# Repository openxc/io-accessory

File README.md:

OpenXC Dock
===========

This repository is a part of the [OpenXC][] project.

This repository contains the documentation and open source design files for an
example OpenXC accessory that provides a generic I/O interface to add sensors
and actuators to a vehicle. The design was originally released by Ford.

This design has yet to be actually prototyped, so YMMV.

## License

Copyright (c) 2014 Ford Motor Company

The electrical and mechanical designs in this repository are available under the
[Creative Commons Attribution 4.0
International](http://creativecommons.org/licenses/by/4.0/deed.en_US) license.

[OpenXC]: http://openxcplatform.com

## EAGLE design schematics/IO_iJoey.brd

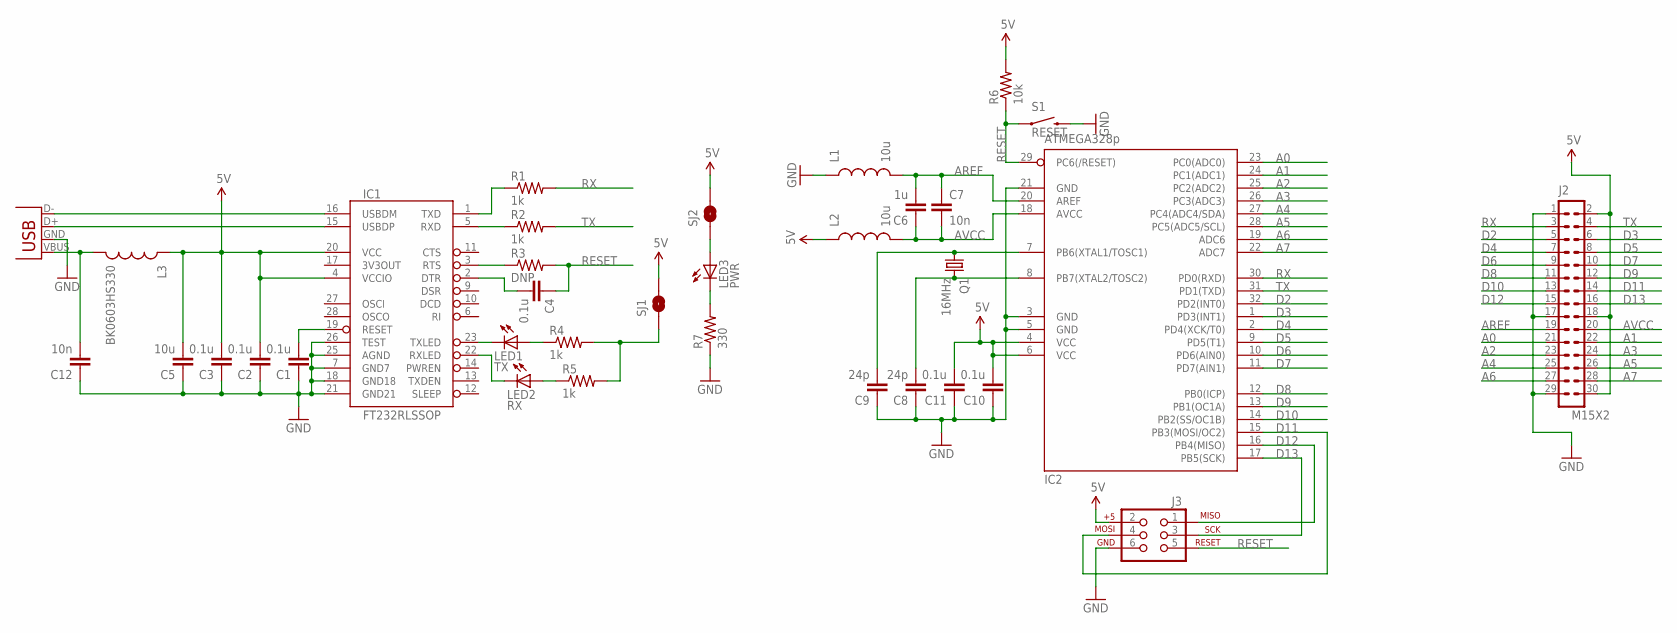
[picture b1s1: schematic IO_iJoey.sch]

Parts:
C1, C2, C3, C4, C10, C11: 0.1u; 0603-CAP
C5: 10u; 0805
C6: 1u; 0603-CAP
C7, C12: 10n; 0603-CAP
C8, C9: 24p; 0603-CAP
IC1: FT232RLSSOP; SSOP28DB
IC2: ATMEGA328p; TQFP32-08
J1: USB-A-H
J2: M15X2; 2X15
J3: AVR_SPI_PRG_6PTH; 2X3
L1, L2: 10u; 0603
L3: BK0603HS330; 0603
LED1: TX; LED-0603
LED2: RX; LED-0603
LED3: PWR; LED-0603
Q1: 16MHz; HC49_GP
R1, R2, R4, R5: 1k; 0603-RES
R3: DNP; 0603-RES
R6: 10k; 0603-RES
R7: 330; 0603-RES
S1: RESET; TACTILE-SWITCH-1101NE
SJ1, SJ2: SOLDERJUMPERNC; SJ_2S

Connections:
5V: C2.2, C3.2, C5.2, C10.2, C11.2, IC1.4 (VCCIO), IC1.20 (VCC), IC2.4 (VCC), IC2.6 (VCC), J2.2, J2.18, J2.30, J3.2, L2.1, L3.1, R6.2, SJ1.2, SJ2.2
A0: IC2.23 (PC0(ADC0)), J2.21
A1: IC2.24 (PC1(ADC1)), J2.22
A2: IC2.25 (PC2(ADC2)), J2.23
A3: IC2.26 (PC3(ADC3)), J2.24
A4: IC2.27 (PC4(ADC4/SDA)), J2.25
A5: IC2.28 (PC5(ADC5/SCL)), J2.26
A6: IC2.19 (ADC6), J2.27
A7: IC2.22 (ADC7), J2.28
AREF: C6.2, C7.1, IC2.20 (AREF), J2.19, L1.2
AVCC: C6.1, C7.2, IC2.18 (AVCC), J2.20, L2.2
D2: IC2.32 (PD2(INT0)), J2.5
D3: IC2.1 (PD3(INT1)), J2.6
D4: IC2.2 (PD4(XCK/T0)), J2.7
D5: IC2.9 (PD5(T1)), J2.8
D6: IC2.10 (PD6(AIN0)), J2.9
D7: IC2.11 (PD7(AIN1)), J2.10
D8: IC2.12 (PB0(ICP)), J2.11
D9: IC2.13 (PB1(OC1A)), J2.12
D10: IC2.14 (PB2(SS/OC1B)), J2.13
D11: IC2.15 (PB3(MOSI/OC2)), J2.14, J3.4
D12: IC2.16 (PB4(MISO)), J2.15, J3.1
D13: IC2.17 (PB5(SCK)), J2.16, J3.3
GND: C1.1, C2.1, C3.1, C5.1, C8.1, C9.1, C10.1, C11.1, C12.1, IC1.7 (GND7), IC1.18 (GND18), IC1.21 (GND21), IC1.25 (AGND), IC1.26 (TEST), IC2.3 (GND), IC2.5 (GND), IC2.21 (GND), J1.GND (VBUS), J2.1, J2.17, J2.29, J3.6, L1.1, R7.1, S1.P$2 (2)
unnamed: IC1.15 (USBDP), J1.D+ (D-)
unnamed: IC1.16 (USBDM), J1.D- (D+)
unnamed: C4.2, IC1.2 (DTR)
unnamed: C1.2, IC1.19 (RESET)
unnamed: C12.2, J1.VBUS (GND), L3.2
unnamed: IC1.3 (RTS), R3.1
unnamed: IC1.5 (RXD), R2.1
unnamed: IC1.1 (TXD), R1.1
unnamed: LED3.C, R7.2
unnamed: IC1.23 (TXLED), LED1.C
unnamed: IC1.22 (RXLED), LED2.C
unnamed: LED2.A, R5.1
unnamed: LED1.A, R4.1
unnamed: R4.2, R5.2, SJ1.1
unnamed: LED3.A, SJ2.1
unnamed: C9.2, IC2.7 (PB6(XTAL1/TOSC1)), Q1.1
unnamed: C8.2, IC2.8 (PB7(XTAL2/TOSC2)), Q1.2
RESET: C4.1, IC2.29 (PC6(/RESET)), J3.5, R3.2, R6.1, S1.P$1 (1)
RX: IC2.30 (PD0(RXD)), J2.3, R1.2
TX: IC2.31 (PD1(TXD)), J2.4, R2.2

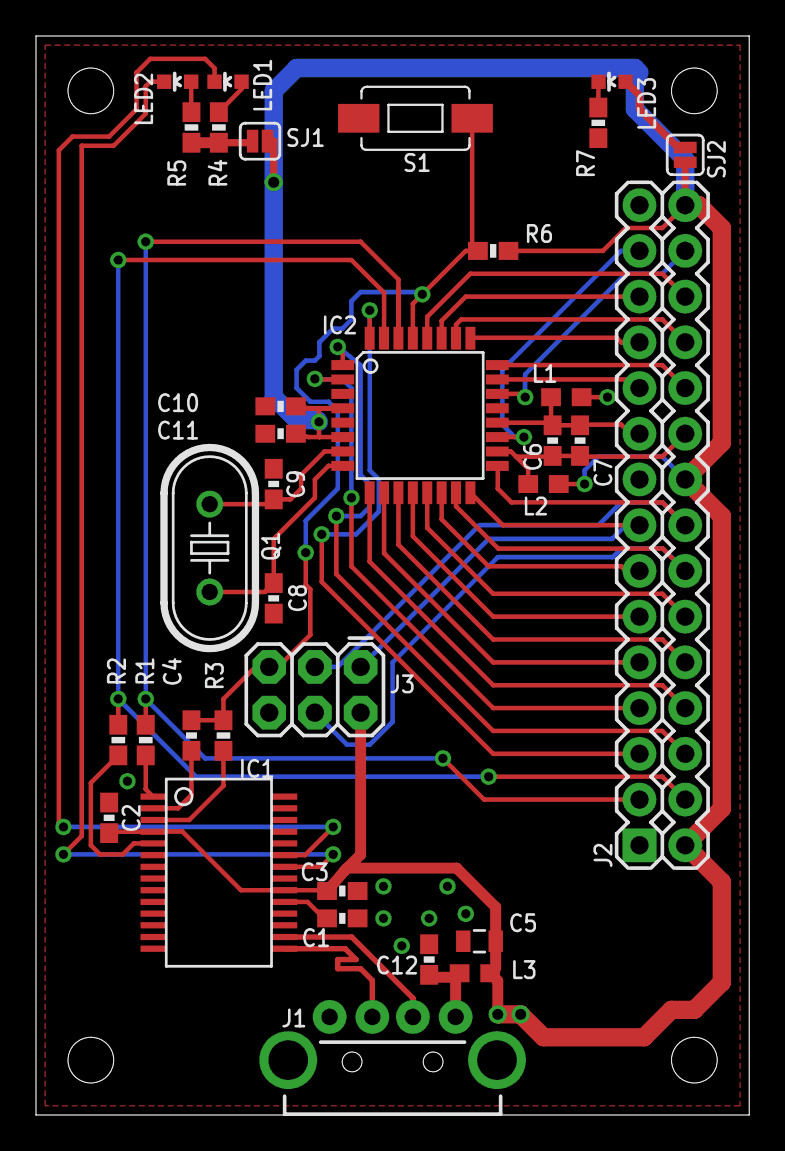
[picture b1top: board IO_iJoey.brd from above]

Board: 2 copper layers, 39.6 x 59.9 mm, 34 parts (0 on the bottom side), 44 nets.

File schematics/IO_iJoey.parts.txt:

Partlist

Exported from IO_iJoey.sch at 11/19/12 4:03 PM

EAGLE Version 6.1.0 Copyright (c) 1988-2012 CadSoft

Assembly variant: 

Part     Value          Device                        Package               Library                    Sheet

C1       0.1u           CAP0603-CAP                   0603-CAP              BUG                        1
C2       0.1u           CAP0603-CAP                   0603-CAP              BUG                        1
C3       0.1u           CAP0603-CAP                   0603-CAP              BUG                        1
C4       0.1u           CAP0603-CAP                   0603-CAP              BUG                        1
C5       10u            CAP0805                       0805                  BUG                        1
C6       1u             CAP0603-CAP                   0603-CAP              BUG                        1
C7       10n            CAP0603-CAP                   0603-CAP              BUG                        1
C8       24p            CAP0603-CAP                   0603-CAP              BUG                        1
C9       24p            CAP0603-CAP                   0603-CAP              BUG                        1
C10      0.1u           CAP0603-CAP                   0603-CAP              BUG                        1
C11      0.1u           CAP0603-CAP                   0603-CAP              BUG                        1
C12      10n            CAP0603-CAP                   0603-CAP              BUG                        1
IC1      FT232RLSSOP    FT232RLSSOP                   SSOP28DB              SparkFun-DigitalIC         1
IC2      ATMEGA328p     MEGA8-AI                      TQFP32-08             atmel                      1
J1       USB-A-H        USB-A-H                       USB-A-H               SparkFun-Connectors        1
J2       M15X2          M15X2                         2X15                  BUG                        1
J3                      AVR_SPI_PRG_6PTH              2X3                   SparkFun-Connectors        1
L1       10u            INDUCTOR0603                  0603                  BUG                        1
L2       10u            INDUCTOR0603                  0603                  BUG                        1
L3       BK0603HS330    INDUCTOR0603                  0603                  BUG                        1
LED1     TX             LED0603                       LED-0603              BUG                        1
LED2     RX             LED0603                       LED-0603              BUG                        1
LED3     PWR            LED0603                       LED-0603              BUG                        1
Q1       16MHz          CRYSTAL-GP                    HC49_GP               BUG                        1
R1       1k             RESISTOR0603-RES              0603-RES              BUG                        1
R2       1k             RESISTOR0603-RES              0603-RES              BUG                        1
R3       DNP            RESISTOR0603-RES              0603-RES              BUG                        1
R4       1k             RESISTOR0603-RES              0603-RES              BUG                        1
R5       1k             RESISTOR0603-RES              0603-RES              BUG                        1
R6       10k            RESISTOR0603-RES              0603-RES              BUG                        1
R7       330            RESISTOR0603-RES              0603-RES              BUG                        1
S1       RESET          SWITCH-MOMENTARY-2-SMD-1101NE TACTILE-SWITCH-1101NE SparkFun-Electromechanical 1

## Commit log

2013-04-19 Initial commit.
2014-03-11 Add README and license for release.

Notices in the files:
parts and their libraries:
SparkFun-Connectors: Licensing: CC v3.0 Share-Alike You are welcome to use this library for commercial purposes.
